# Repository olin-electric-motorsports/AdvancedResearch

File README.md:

# AdvancedResearch

2020 Advanced Research

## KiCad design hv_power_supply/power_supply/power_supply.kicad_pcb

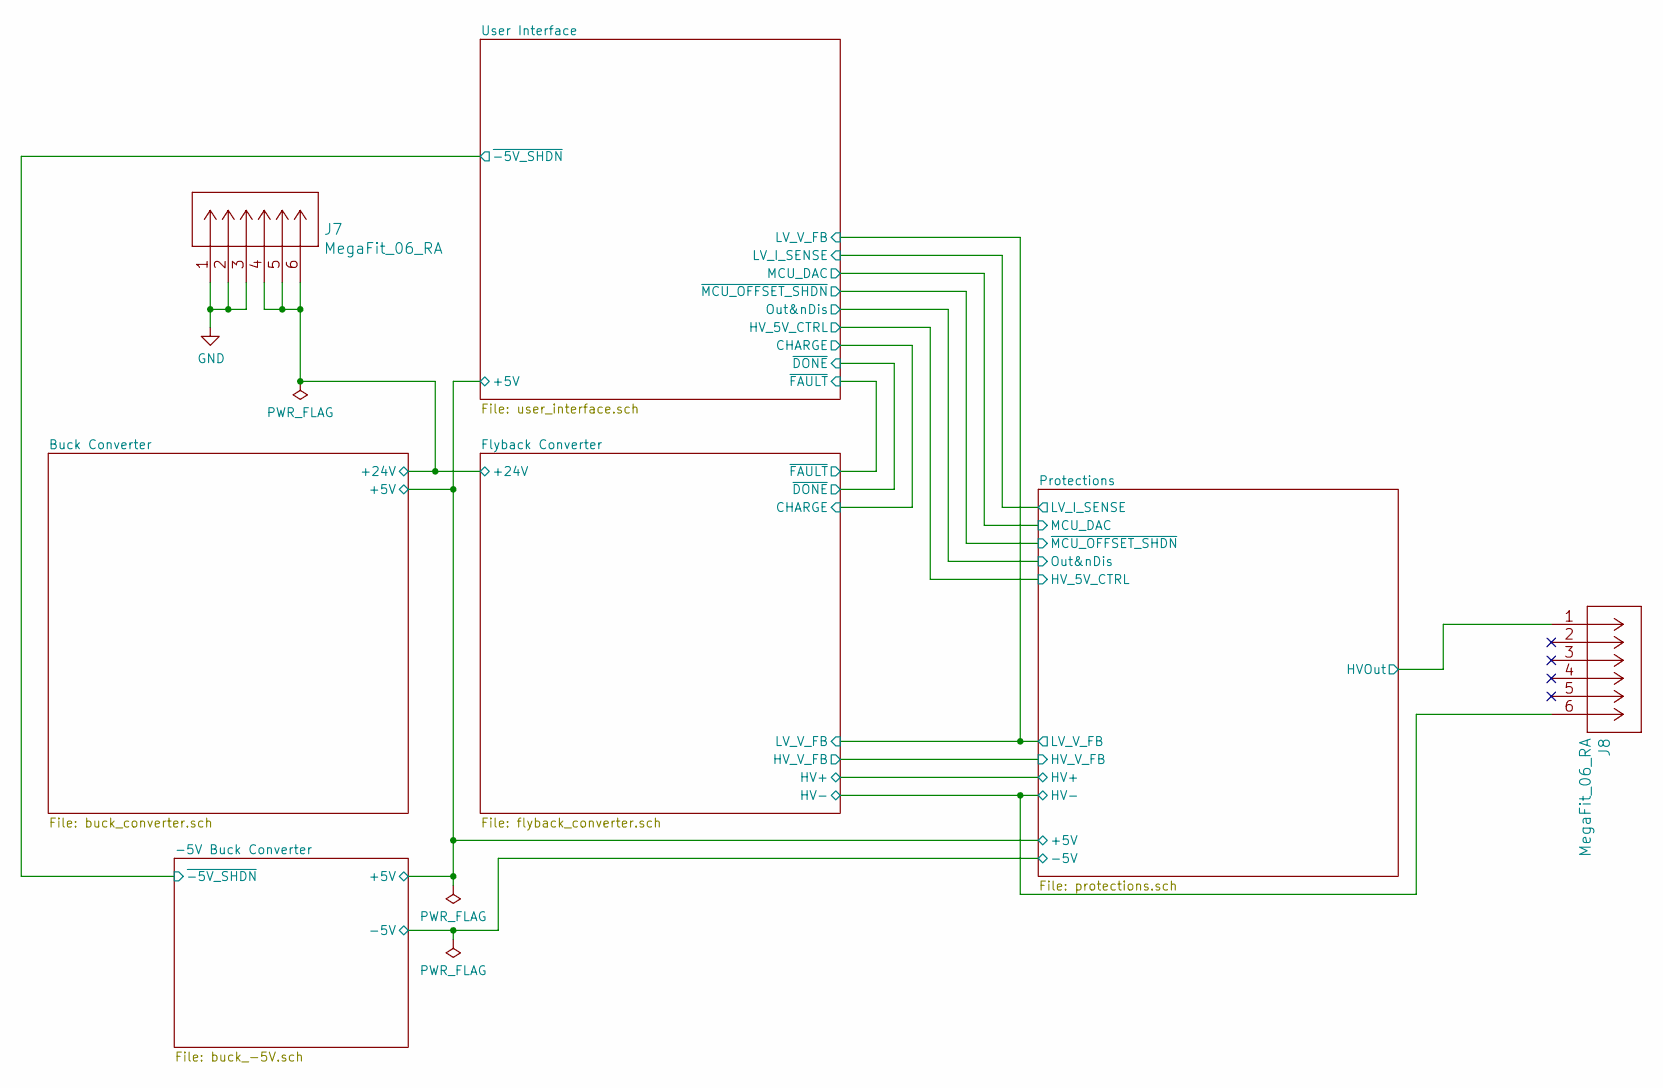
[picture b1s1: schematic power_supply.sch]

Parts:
J7, J8: MegaFit_06_RA; MPN 0768250006

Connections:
/Buck Converter/+24V: J7.4, J7.5, J7.6; also elsewhere on the board
/Flyback Converter/HV-: J8.6; also elsewhere on the board
/Protections/HVOut: J8.1; also elsewhere on the board
GND: J7.1, J7.2, J7.3; also elsewhere on the board

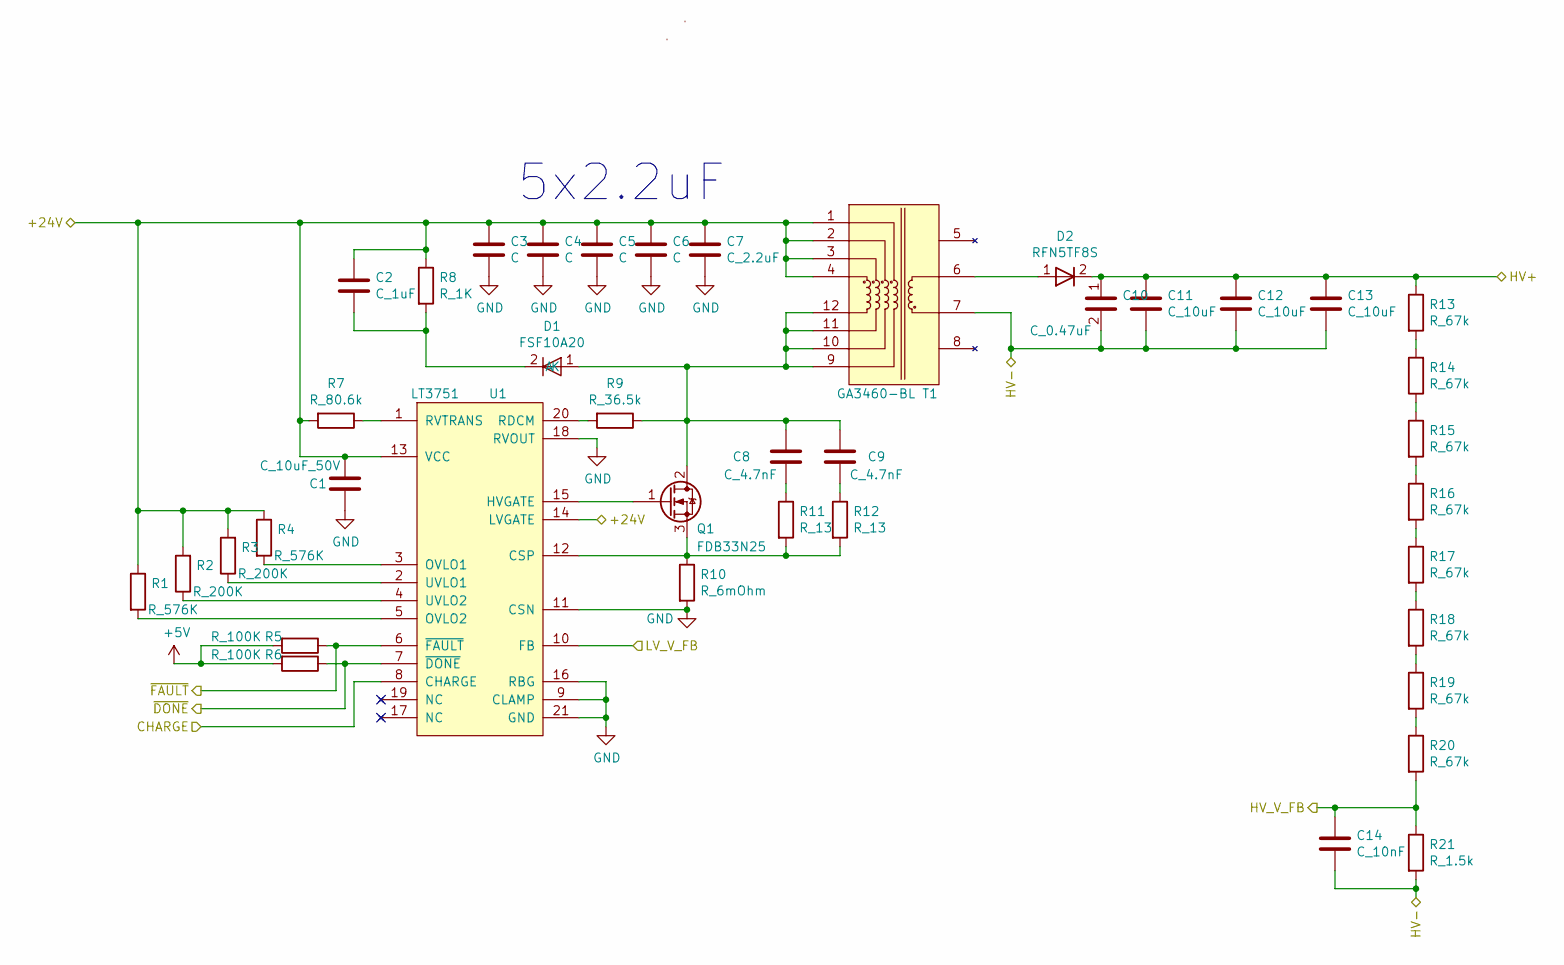
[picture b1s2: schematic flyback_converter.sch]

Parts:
C1: C_10uF_50V; C_0805_OEM; MPN GRM21BR61H106KE43L
C2: C_1uF; C_0805_OEM
C3, C4, C5, C6: C; C_0805_OEM
C7: C_2.2uF; C_0805_OEM
C8, C9: C_4.7nF; C_1206_OEM; MPN C1206C472KCRACTU
C10: C_0.47uF; 1812(4532Metric); MPN C4532X7T2W474K230KA
C11, C12, C13: C_10uF; C_10uF_450V
C14: C_10nF; C_0805_OEM; MPN 1276-1015-1-ND
D1: FSF10A20; TO-220NFM; MPN FSF10A20
D2: RFN5TF8S; TO-220NFM
Q1: FDB33N25; D2PAK; MPN FDB33N25TM
R1, R4: R_576K; R_0805_OEM; MPN 541-576KCCT-ND
R2, R3: R_200K; R_0805_OEM; MPN P300KDACT-ND
R5, R6: R_100K; R_0805_OEM; MPN P100KCCT-ND
R7: R_80.6k; R_0805_OEM; MPN RT0805BRD0780K6L
R8: R_1K; R_2512_OEM; MPN CHP2512-FX-1001ELF
R9: R_36.5k; R_0805_OEM; MPN RT0805BRD0736K5L
R10: R_6mOhm; R_2512_LARGE; MPN LRMAP2512-R006FT4
R11, R12: R_13; R_2512_LARGE; MPN 352113RFT
R13, R14, R15, R16, R17, R18, R19, R20: R_67k; R_0805_OEM; MPN CRCW080567K0FKTA
R21: R_1.5k; R_2010_Vishay; MPN CRCW20101K50FKEF
T1: GA3460-BL; MPN 994-GA3460-BL
U1: LT3751; TSSOP-20_EXPOSED_PAD; MPN LT3751EFE#TRPBF

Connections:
+5V: R5.2, R6.2; also elsewhere on the board
/Buck Converter/+24V: C1.2, C2.1, C3.1, C4.1, C5.1, C6.1, C7.1, R1.1, R2.2, R3.2, R4.1, R7.2, R8.1, T1.1, T1.2, T1.3, T1.4, U1.13 (VCC), U1.14 (LVGATE); also elsewhere on the board
/Flyback Converter/CHARGE: U1.8 (CHARGE); also elsewhere on the board
/Flyback Converter/HV+: C10.1, C11.1, C12.1, C13.1, D2.2, R13.1; also elsewhere on the board
/Flyback Converter/HV-: C10.2, C11.2, C12.2, C13.2, C14.2, R21.2, T1.7; also elsewhere on the board
/Flyback Converter/HV_V_FB: C14.1, R20.2, R21.1; also elsewhere on the board
/Flyback Converter/LV_V_FB: U1.10 (FB); also elsewhere on the board
/Flyback Converter/~DONE: R6.1, U1.7 (~DONE); also elsewhere on the board
/Flyback Converter/~FAULT: R5.1, U1.6 (~FAULT); also elsewhere on the board
GND: C1.1, C3.2, C4.2, C5.2, C6.2, C7.2, R10.2, U1.9 (CLAMP), U1.11 (CSN), U1.16 (RBG), U1.18 (RVOUT), U1.21 (GND); also elsewhere on the board
unnamed: C2.2, D1.2 (K), R8.2
unnamed: C8.1, C9.1, D1.1 (A), Q1.2, R9.1, T1.9, T1.10, T1.11, T1.12
unnamed: C8.2, R11.1
unnamed: C9.2, R12.1
unnamed: D2.1, T1.6
unnamed: Q1.1, U1.15 (HVGATE)
unnamed: Q1.3, R10.1, R11.2, R12.2, U1.12 (CSP)
unnamed: R1.2, U1.5 (OVLO2)
unnamed: R2.1, U1.4 (UVLO2)
unnamed: R3.1, U1.2 (UVLO1)
unnamed: R4.2, U1.3 (OVLO1)
unnamed: R7.1, U1.1 (RVTRANS)
unnamed: R9.2, U1.20 (RDCM)
unnamed: R13.2, R14.2
unnamed: R14.1, R15.1
unnamed: R15.2, R16.1
unnamed: R16.2, R17.1
unnamed: R17.2, R18.1
unnamed: R18.2, R19.1
unnamed: R19.2, R20.1

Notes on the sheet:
5x2.2uF

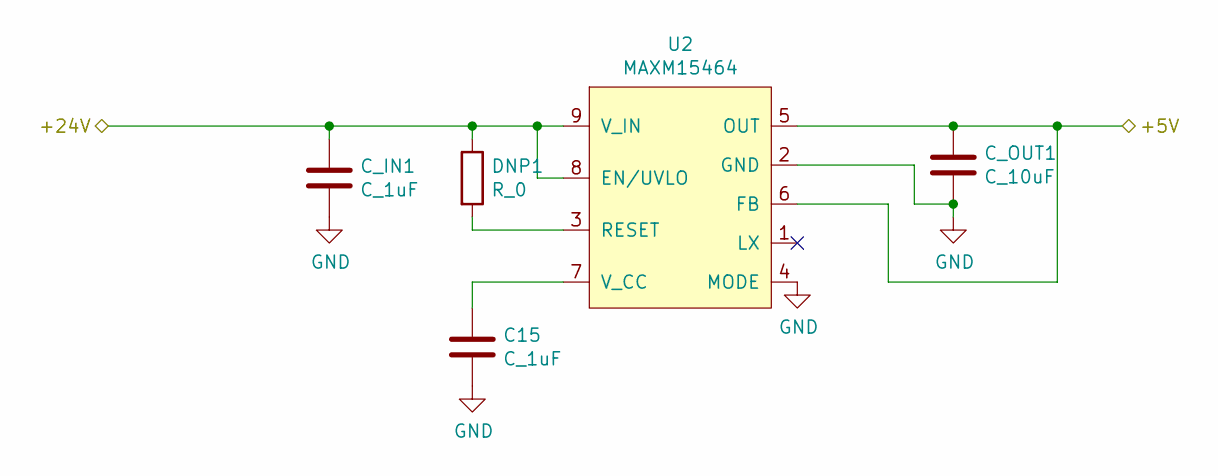
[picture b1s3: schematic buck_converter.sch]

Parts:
C15: C_1uF; C_0805_OEM
C_IN1: C_1uF; C_0805_OEM
C_OUT1: C_10uF; C_0805_OEM; MPN 1276-1052-1-ND
DNP1: R_0; R_0603_1608Metric; MPN P0.0GCT-ND
U2: MAXM15464; MPN MAXM15464AMB+

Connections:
+5V: C_OUT1.1, U2.5 (OUT), U2.6 (FB); also elsewhere on the board
/Buck Converter/+24V: C_IN1.1, DNP1.1, U2.8 (EN/UVLO), U2.9 (V_IN); also elsewhere on the board
GND: C15.2, C_IN1.2, C_OUT1.2, U2.2 (GND), U2.4 (MODE); also elsewhere on the board
unnamed: C15.1, U2.7 (V_CC)
unnamed: DNP1.2, U2.3 (RESET)

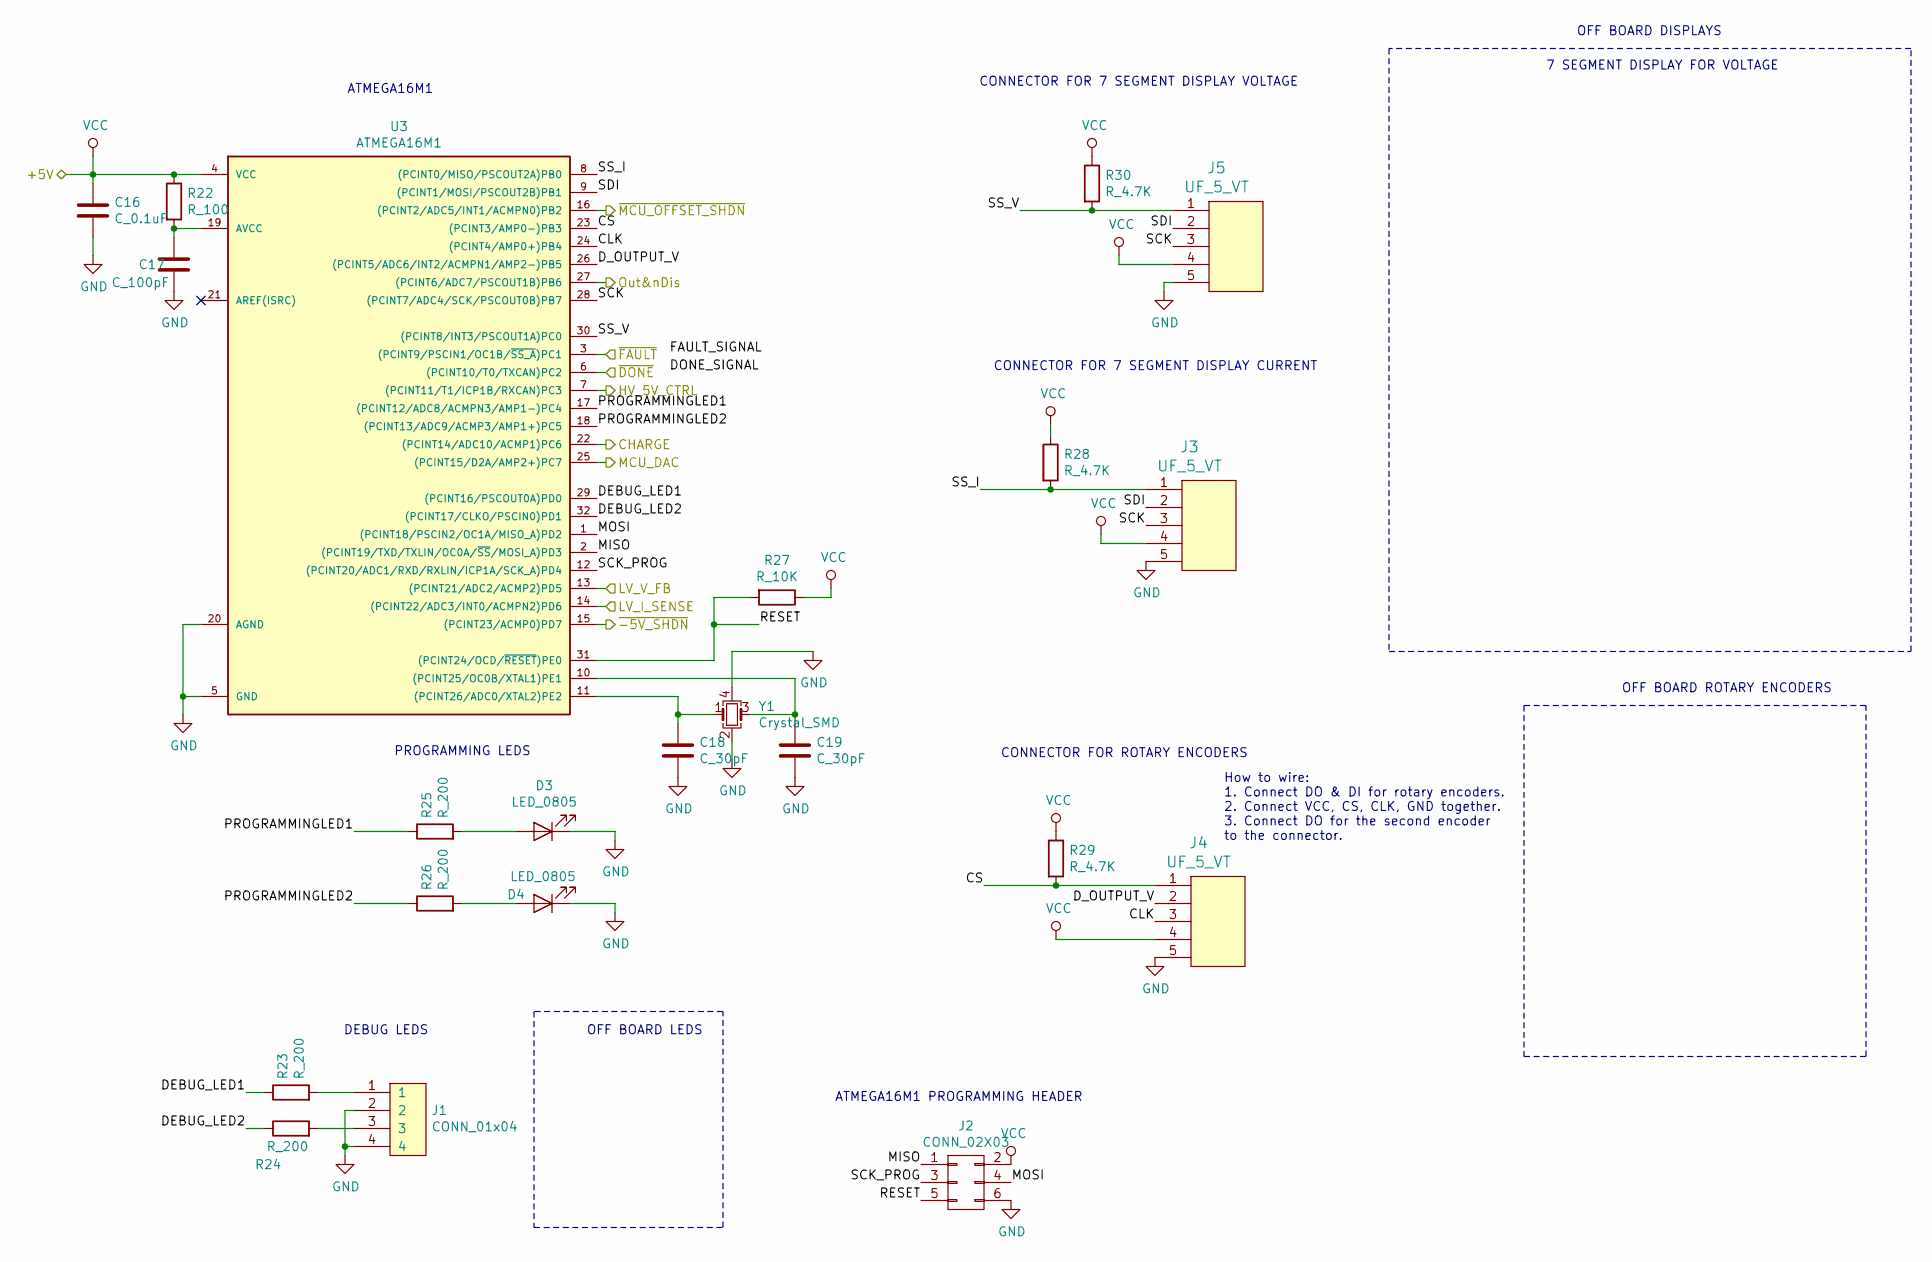
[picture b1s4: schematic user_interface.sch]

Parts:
C16: C_0.1uF; C_0805_OEM; MPN 478-3352-1-ND
C17: C_100pF; C_0805_OEM; MPN 732-7852-1-ND
C18, C19: C_30pF; C_0805_OEM; MPN 1276-1130-1-ND
D3, D4: LED_0805; LED_0805_OEM; MPN 475-1410-1-ND
J1: CONN_01x04; Pin_Header_Straight_1x04_Pitch2.54mm; MPN 732-5317-ND
J2: CONN_02X03; Pin_Header_Straight_2x03; MPN 609-3234-ND
J3, J4, J5: UF_5_VT; Ultrafit_5; MPN WM11667-ND
R22: R_100; R_0805_OEM; MPN RNCP0805FTD100RCT-ND
R23, R24, R25, R26: R_200; R_0805_OEM; MPN RMCF0805JT200RCT-ND
R27: R_10K; R_0805_OEM; MPN CRS0805-FX-1002ELFCT-ND
R28, R29, R30: R_4.7K; R_0805_OEM; MPN 311-4.7KARCT-ND
U3: ATMEGA16M1; TQFP-32_7x7mm_Pitch0.8mm; MPN ATMEGA16M1-AU-ND
Y1: Crystal_SMD; Crystal_SMD_FA238; MPN 887-1125-1-ND

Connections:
+5V: C16.1, J2.2, J3.4, J4.4, J5.4, R22.1, R27.1, R28.1, R29.1, R30.1, U3.4 (VCC); also elsewhere on the board
/-5V Buck Converter/~-5V_SHDN: U3.15 ((PCINT23/ACMP0)PD7); also elsewhere on the board
/Flyback Converter/CHARGE: U3.22 ((PCINT14/ADC10/ACMP1)PC6); also elsewhere on the board
/Flyback Converter/LV_V_FB: U3.13 ((PCINT21/ADC2/ACMP2)PD5); also elsewhere on the board
/Flyback Converter/~DONE: U3.6 ((PCINT10/T0/TXCAN)PC2); also elsewhere on the board
/Flyback Converter/~FAULT: U3.3 ((PCINT9/PSCIN1/OC1B/~SS_A~)PC1); also elsewhere on the board
/Protections/HV_5V_CTRL: U3.7 ((PCINT11/T1/ICP1B/RXCAN)PC3); also elsewhere on the board
/Protections/LV_I_SENSE: U3.14 ((PCINT22/ADC3/INT0/ACMPN2)PD6); also elsewhere on the board
/Protections/MCU_DAC: U3.25 ((PCINT15/D2A/AMP2+)PC7); also elsewhere on the board
/Protections/Out&nDis: U3.27 ((PCINT6/ADC7/PSCOUT1B)PB6); also elsewhere on the board
/Protections/~MCU_OFFSET_SHDN: U3.16 ((PCINT2/ADC5/INT1/ACMPN0)PB2); also elsewhere on the board
/User Interface/CLK: J4.3, U3.24 ((PCINT4/AMP0+)PB4)
/User Interface/CS: J4.1, R29.2, U3.23 ((PCINT3/AMP0-)PB3)
/User Interface/DEBUG_LED1: R23.1, U3.29 ((PCINT16/PSCOUT0A)PD0)
/User Interface/DEBUG_LED2: R24.1, U3.32 ((PCINT17/CLKO/PSCIN0)PD1)
/User Interface/D_OUTPUT_V: J4.2, U3.26 ((PCINT5/ADC6/INT2/ACMPN1/AMP2-)PB5)
/User Interface/MISO: J2.1, U3.2 ((PCINT19/TXD/TXLIN/OC0A/~SS~/MOSI_A)PD3)
/User Interface/MOSI: J2.4, U3.1 ((PCINT18/PSCIN2/OC1A/MISO_A)PD2)
/User Interface/PROGRAMMINGLED1: R25.1, U3.17 ((PCINT12/ADC8/ACMPN3/AMP1-)PC4)
/User Interface/PROGRAMMINGLED2: R26.1, U3.18 ((PCINT13/ADC9/ACMP3/AMP1+)PC5)
/User Interface/RESET: J2.5, R27.2, U3.31 ((PCINT24/OCD/~RESET~)PE0)
/User Interface/SCK: J3.3, J5.3, U3.28 ((PCINT7/ADC4/SCK/PSCOUT0B)PB7)
/User Interface/SCK_PROG: J2.3, U3.12 ((PCINT20/ADC1/RXD/RXLIN/ICP1A/SCK_A)PD4)
/User Interface/SDI: J3.2, J5.2, U3.9 ((PCINT1/MOSI/PSCOUT2B)PB1)
/User Interface/SS_I: J3.1, R28.2, U3.8 ((PCINT0/MISO/PSCOUT2A)PB0)
/User Interface/SS_V: J5.1, R30.2, U3.30 ((PCINT8/INT3/PSCOUT1A)PC0)
GND: C16.2, C17.2, C18.2, C19.2, D3.1 (K), D4.1 (K), J1.2, J1.4, J2.6, J3.5, J4.5, J5.5, U3.5 (GND), U3.20 (AGND), Y1.2, Y1.4; also elsewhere on the board
unnamed: C17.1, R22.2, U3.19 (AVCC)
unnamed: C18.1, U3.11 ((PCINT26/ADC0/XTAL2)PE2), Y1.1
unnamed: C19.1, U3.10 ((PCINT25/OC0B/XTAL1)PE1), Y1.3
unnamed: D3.2 (A), R25.2
unnamed: D4.2 (A), R26.2
unnamed: J1.1, R23.2
unnamed: J1.3, R24.2

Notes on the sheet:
ATMEGA16M1
PROGRAMMING LEDS
ATMEGA16M1 PROGRAMMING HEADER
CONNECTOR FOR 7 SEGMENT DISPLAY VOLTAGE
CONNECTOR FOR 7 SEGMENT DISPLAY CURRENT
DEBUG LEDS
CONNECTOR FOR ROTARY ENCODERS
How to wire: 1. Connect DO & DI for rotary encoders. 2. Connect VCC, CS, CLK, GND together. 3. Connect DO for the second encoder to the connector.
OFF BOARD LEDS
OFF BOARD DISPLAYS
OFF BOARD ROTARY ENCODERS
7 SEGMENT DISPLAY FOR VOLTAGE

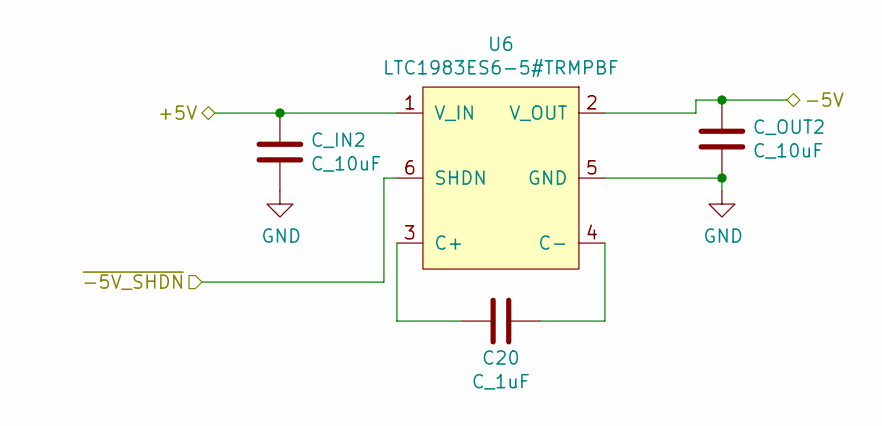
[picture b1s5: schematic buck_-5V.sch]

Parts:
C20: C_1uF; C_0805_OEM
C_IN2: C_10uF; C_0805_OEM; MPN 1276-1052-1-ND
C_OUT2: C_10uF; C_0805_OEM; MPN 1276-1052-1-ND
U6: LTC1983ES6-5#TRMPBF

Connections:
+5V: C_IN2.1, U6.1 (V_IN); also elsewhere on the board
/-5V Buck Converter/-5V: C_OUT2.1, U6.2 (V_OUT); also elsewhere on the board
/-5V Buck Converter/~-5V_SHDN: U6.6 (SHDN); also elsewhere on the board
GND: C_IN2.2, C_OUT2.2, U6.5 (GND); also elsewhere on the board
unnamed: C20.1, U6.3 (C+)
unnamed: C20.2, U6.4 (C-)

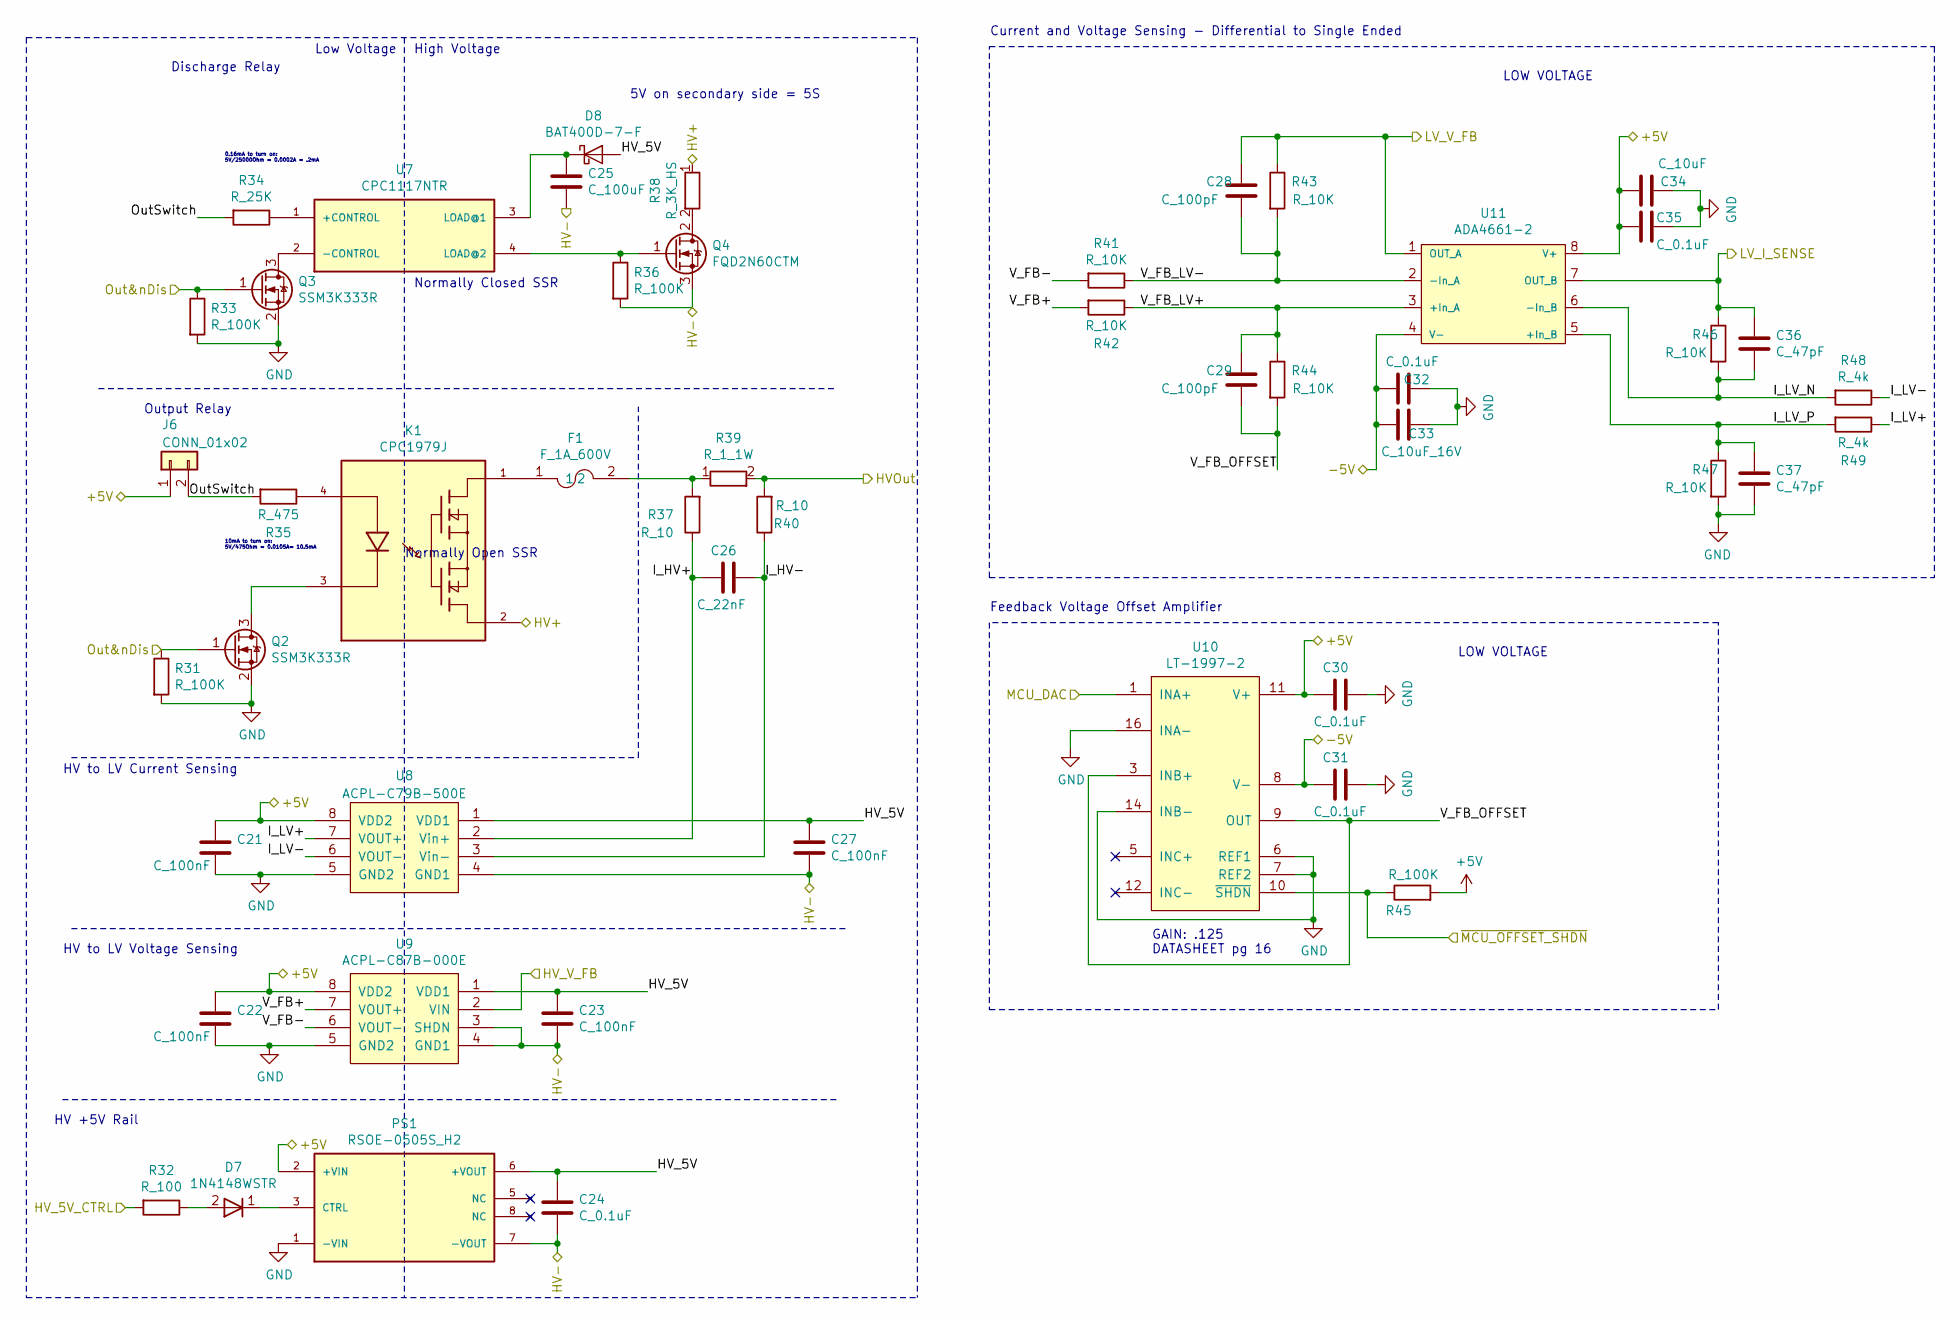
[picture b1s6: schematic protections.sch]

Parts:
C21, C22, C23, C27: C_100nF; C_0603_1608Metric; MPN 1276-6717-1-ND
C24, C30, C31, C32, C35: C_0.1uF; C_0805_OEM; MPN 478-3352-1-ND
C25: C_100uF; C_1812_4532Metric; MPN 445-1413-1-ND
C26: C_22nF; C_0805_OEM; MPN C0805C223G3GEC7800
C28, C29: C_100pF; C_0805_OEM; MPN 732-7852-1-ND
C33: C_10uF_16V; C_0805_OEM; MPN 1276-2399-1-ND
C34: C_10uF; C_0805_OEM; MPN 1276-2399-1-ND
C36, C37: C_47pF; C_0805_OEM; MPN CDR31BP470BKUS7185
D7: 1N4148WSTR; SOD-323; MPN 1N4148WSTR
D8: BAT400D-7-F; SOT-23-3_OEM
F1: F_1A_600V; Fuse_1A_600V
J6: CONN_01x02; PinHeader_1x02_P2.54mm_Vertical; MPN 732-5315-ND
K1: CPC1979J; TO381P2016X515X2916-4; PARTREV R10
PS1: RSOE-0505S_H2; H2; PARTREV 4/2020
Q2, Q3: SSM3K333R; SOT-23F; MPN SSM3K333RLFCT-ND
Q4: FQD2N60CTM; DPAK229P990X239-4N; MPN FDB33N25TM
R31, R33, R36, R45: R_100K; R_0805_OEM; MPN P100KCCT-ND
R32: R_100; R_0805_OEM; MPN RNCP0805FTD100RCT-ND
R34: R_25K; R_0805_OEM; MPN A124124CT-ND
R35: R_475; R_0805_OEM; MPN 311-475CRCT-ND
R37, R40: R_10; R_0805_OEM; MPN ERJ-P06F10R0V
R38: R_3K_HS; R_3k_HS_TO247; MPN AP1013KJ-ND
R39: R_1_1W; R_2512_LARGE
R41, R42, R43, R44, R46, R47: R_10K; R_0805_OEM; MPN CRS0805-FX-1002ELFCT-ND
R48, R49: R_4k; R_0805_OEM; MPN CRCW08054K00FKTA
U7: CPC1117NTR; SOIC254P610X218-4N
U8: ACPL-C79B-500E; SSO-8; MPN ACPL-C79B-500E
U9: ACPL-C87B-000E; SSO-8
U10: LT-1997-2; 16(12)-MSOP; MPN LT1997HMS-2#PBF
U11: ADA4661-2; SOP65P490X110-8N; MPN ADA4661-2ARMZ-RL

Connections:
+5V: C21.1, C22.1, C30.1, C34.1, C35.2, J6.1, PS1.2 (+VIN), R45.2, U8.8 (VDD2), U9.8 (VDD2), U10.11 (V+), U11.8 (V+); also elsewhere on the board
/-5V Buck Converter/-5V: C31.1, C32.1, C33.1, U10.8 (V-), U11.4 (V-); also elsewhere on the board
/Flyback Converter/HV+: K1.2, R38.1; also elsewhere on the board
/Flyback Converter/HV-: C23.2, C24.2, C25.2, C27.2, PS1.7 (-VOUT), Q4.3, R36.2, U8.4 (GND1), U9.3 (SHDN), U9.4 (GND1); also elsewhere on the board
/Flyback Converter/HV_V_FB: U9.2 (VIN); also elsewhere on the board
/Flyback Converter/LV_V_FB: C28.1, R43.1, U11.1 (OUT_A); also elsewhere on the board
/Protections/HVOut: R39.2, R40.2; also elsewhere on the board
/Protections/HV_5V: C23.1, C24.1, C27.1, D8.2 (A), PS1.6 (+VOUT), U8.1 (VDD1), U9.1 (VDD1)
/Protections/HV_5V_CTRL: R32.2; also elsewhere on the board
/Protections/I_HV+: C26.1, R37.1, U8.2 (Vin+)
/Protections/I_HV-: C26.2, R40.1, U8.3 (Vin-)
/Protections/I_LV+: R49.1, U8.7 (VOUT+)
/Protections/I_LV-: R48.1, U8.6 (VOUT-)
/Protections/I_LV_N: C36.2, R46.2, R48.2, U11.6 (-In_B)
/Protections/I_LV_P: C37.1, R47.1, R49.2, U11.5 (+In_B)
/Protections/LV_I_SENSE: C36.1, R46.1, U11.7 (OUT_B); also elsewhere on the board
/Protections/MCU_DAC: U10.1 (INA+); also elsewhere on the board
/Protections/Out&nDis: Q2.1 (G), Q3.1 (G), R31.1, R33.1; also elsewhere on the board
/Protections/OutSwitch: J6.2, R34.2, R35.2
/Protections/V_FB+: R42.2, U9.7 (VOUT+)
/Protections/V_FB-: R41.2, U9.6 (VOUT-)
/Protections/V_FB_LV+: C29.1, R42.1, R44.1, U11.3 (+In_A)
/Protections/V_FB_LV-: C28.2, R41.1, R43.2, U11.2 (-In_A)
/Protections/V_FB_OFFSET: C29.2, R44.2, U10.3 (INB+), U10.9 (OUT)
/Protections/~MCU_OFFSET_SHDN: R45.1, U10.10 (~SHDN); also elsewhere on the board
GND: C21.2, C22.2, C30.2, C31.2, C32.2, C33.2, C34.2, C35.1, C37.2, PS1.1 (-VIN), Q2.2 (S), Q3.2 (S), R31.2, R33.2, R47.2, U8.5 (GND2), U9.5 (GND2), U10.6 (REF1), U10.7 (REF2), U10.14 (INB-), U10.16 (INA-); also elsewhere on the board
unnamed: C25.1, D8.1 (K), U7.3 (LOAD@1)
unnamed: D7.1, PS1.3 (CTRL)
unnamed: D7.2, R32.1
unnamed: F1.1, K1.1
unnamed: F1.2, R37.2, R39.1
unnamed: K1.3, Q2.3 (D)
unnamed: K1.4, R35.1
unnamed: Q3.3 (D), U7.2 (-CONTROL)
unnamed: Q4.1, R36.1, U7.4 (LOAD@2)
unnamed: Q4.2, R38.2
unnamed: R34.1, U7.1 (+CONTROL)

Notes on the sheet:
Discharge Relay
Output Relay
5V on secondary side = 5S
Low Voltage
High Voltage
0.16mA to turn on: 5V/25000Ohm = 0.0002A = .2mA
Normally Closed SSR
Normally Open SSR
10mA to turn on: 5V/475Ohm = 0.0105A= 10.5mA
GAIN: .125 DATASHEET pg 16
HV to LV Current Sensing
HV to LV Voltage Sensing
HV +5V Rail
Feedback Voltage Offset Amplifier
LOW VOLTAGE
Current and Voltage Sensing - Differential to Single Ended

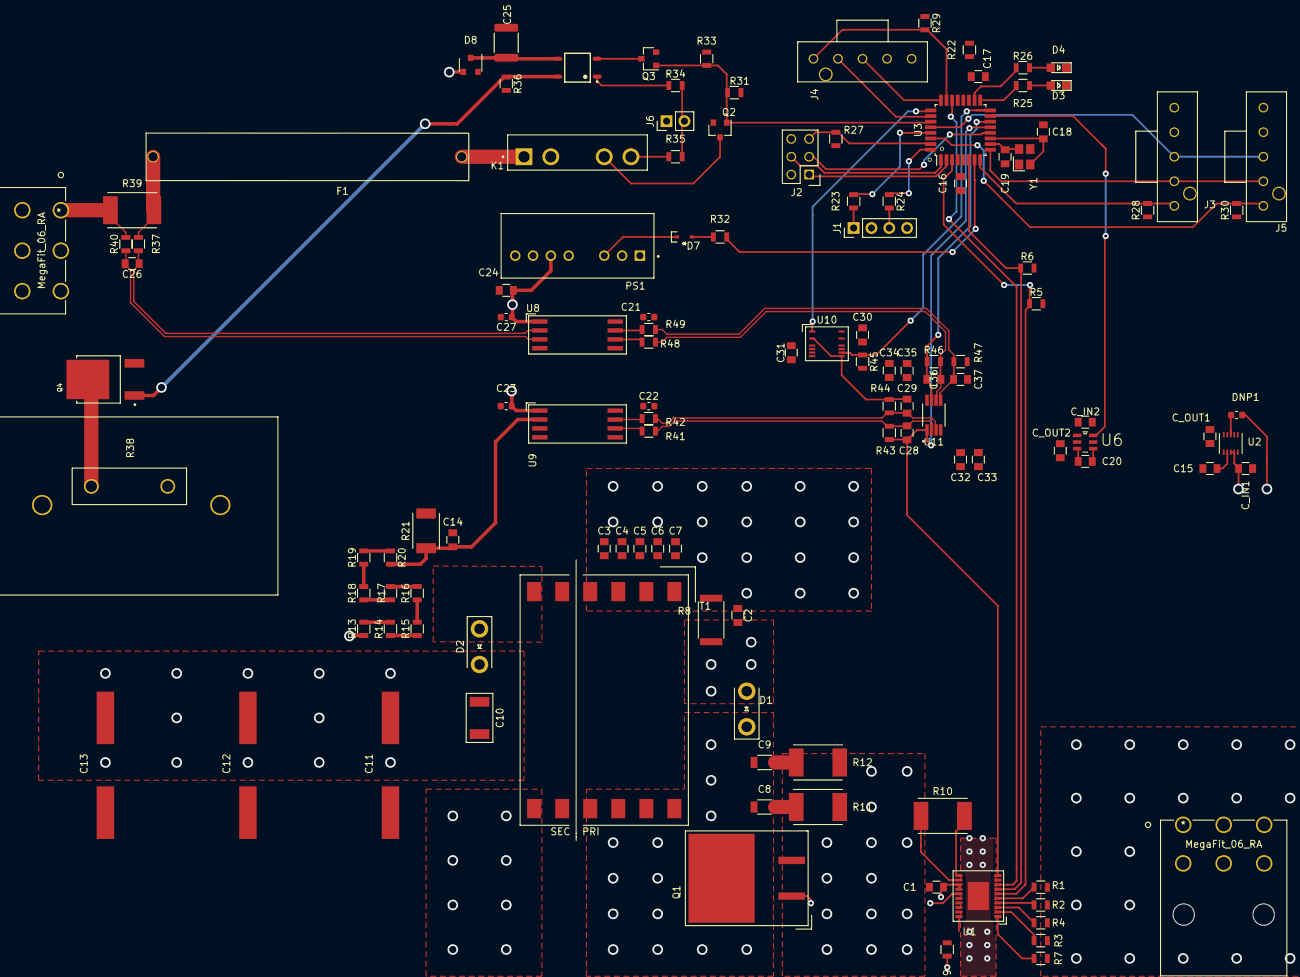
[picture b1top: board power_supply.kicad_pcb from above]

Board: 4 copper layers, 123 parts (0 on the bottom side), 88 nets.

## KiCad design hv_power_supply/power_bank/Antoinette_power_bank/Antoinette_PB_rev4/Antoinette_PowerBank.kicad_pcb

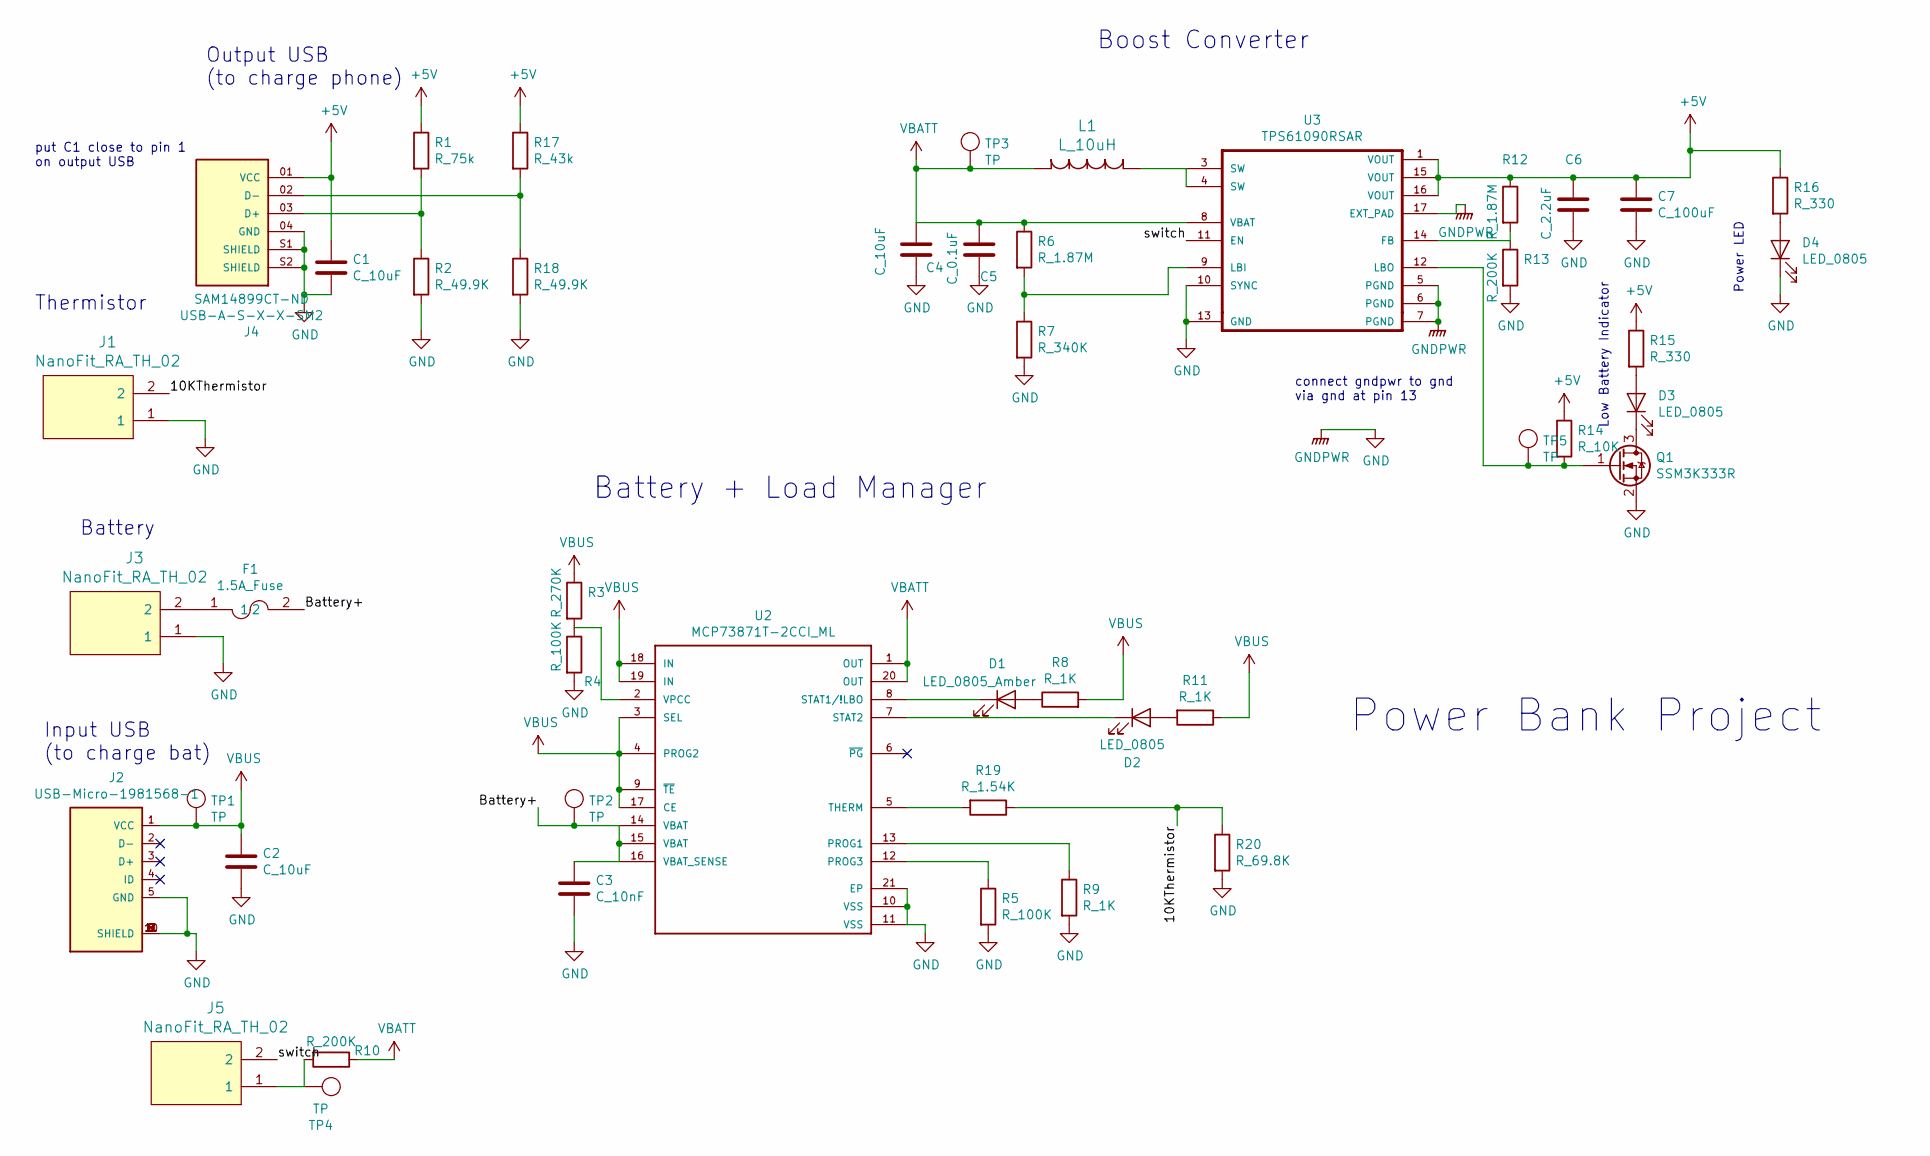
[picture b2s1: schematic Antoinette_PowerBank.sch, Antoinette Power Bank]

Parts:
C1, C2, C4: C_10uF; C_0805_OEM; MPN 1276-1052-1-ND
C3: C_10nF; C_0805_OEM; MPN 1276-1015-1-ND
C5: C_0.1uF; C_0805_OEM; MPN 478-3352-1-ND
C6: C_2.2uF; C_0805_OEM
C7: C_100uF; C_1812_4532Metric; MPN 445-1413-1-ND
D1: LED_0805_Amber; LED_0805_OEM; MPN L71517CT-ND
D2, D3, D4: LED_0805; LED_0805_OEM; MPN 475-1410-1-ND
F1: 1.5A_Fuse; Fuse_1206; MPN F1462CT-ND
J1, J3, J5: NanoFit_RA_TH_02; NanoFit_Molex_1x02x2.50mm_Angled_OEM; MPN WM14972-ND
J2: USB-Micro-1981568-1; TE_1981568-1; MPN 1981568-1
J4: USB-A-S-X-X-SM2; SAMTEC_USB-A-S-X-X-SM2; MPN SAM14899CT-ND
L1: L_10uH; BournsInductor; MPN SDE0805A-100M
Q1: SSM3K333R; SOT-23F; MPN SSM3K333RLFCT-ND
R1: R_75k; R_0805_OEM
R2, R18: R_49.9K; R_0805_OEM
R3: R_270K; R_0805_OEM; MPN P270KDACT-ND
R4, R5: R_100K; R_0805_OEM; MPN P100KCCT-ND
R6, R12: R_1.87M; R_0805_OEM; MPN RMCF0805FT1M82CT-ND
R7: R_340K; R_0805_OEM; MPN P300KDACT-ND
R8, R9, R11: R_1K; R_0805_OEM; MPN RNCP0805FTD1K00CT-ND
R10, R13: R_200K; R_0805_OEM; MPN P300KDACT-ND
R14: R_10K; R_0805_OEM; MPN CRS0805-FX-1002ELFCT-ND
R15, R16: R_330; R_0805_OEM; MPN RMCF0805FT330RCT-ND
R17: R_43k; R_0805_OEM
R19: R_1.54K; R_0805_OEM; MPN ERJ-6ENF1541V
R20: R_69.8K; R_0805_OEM; MPN ERJ-6ENF6982V
TP1, TP2, TP3, TP4, TP5: TP; tp_1.6mm; MPN 36-5006-ND
U2: MCP73871T-2CCI_ML; MCP73871T
U3: TPS61090RSAR

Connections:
+5V: C1.1, C6.1, C7.1, J4.01 (VCC), R1.1, R12.1, R14.1, R15.1, R16.1, R17.1, U3.1 (VOUT), U3.15 (VOUT), U3.16 (VOUT)
+BATT: C4.1, C5.1, L1.2, R6.1, R10.1, TP3.1, U2.1 (OUT), U2.20 (OUT), U3.8 (VBAT)
/10KThermistor: J1.2, R19.1, R20.1
/Battery+: C3.1, F1.2, TP2.1, U2.14 (VBAT), U2.15 (VBAT), U2.16 (VBAT_SENSE)
/switch: J5.2, U3.11 (EN)
GND: C1.2, C2.2, C3.2, C4.2, C5.2, C6.2, C7.2, D4.1 (K), J1.1, J2.5 (GND), J2.6 (SHIELD), J2.7 (SHIELD), J2.8 (SHIELD), J2.9 (SHIELD), J2.10 (SHIELD), J2.11 (SHIELD), J3.1, J4.04 (GND), J4.S1 (SHIELD), J4.S2 (SHIELD), Q1.2 (S), R2.2, R4.2, R5.2, R7.2, R9.2, R13.2, R18.2, R20.2, U2.10 (VSS), U2.11 (VSS), U2.21 (EP), U3.5 (PGND), U3.6 (PGND), U3.7 (PGND), U3.10 (SYNC), U3.13 (GND), U3.17 (EXT_PAD)
unnamed: D1.1 (K), U2.8 (STAT1/!LBO)
unnamed: D1.2 (A), R8.1
unnamed: D2.1 (K), U2.7 (STAT2)
unnamed: D2.2 (A), R11.2
unnamed: D3.1 (K), Q1.3 (D)
unnamed: D3.2 (A), R15.2
unnamed: D4.2 (A), R16.2
unnamed: F1.1, J3.2
unnamed: J4.02 (D-), R17.2, R18.1
unnamed: J4.03 (D+), R1.2, R2.1
unnamed: J5.1, R10.2, TP4.1
unnamed: L1.1, U3.3 (SW), U3.4 (SW)
unnamed: Q1.1 (G), R14.2, TP5.1, U3.12 (LBO)
unnamed: R3.2, R4.1, U2.2 (VPCC)
unnamed: R5.1, U2.12 (PROG3)
unnamed: R6.2, R7.1, U3.9 (LBI)
unnamed: R9.1, U2.13 (PROG1)
unnamed: R12.2, R13.1, U3.14 (FB)
unnamed: R19.2, U2.5 (THERM)
VBUS: C2.1, J2.1 (VCC), R3.1, R8.2, R11.1, TP1.1, U2.3 (SEL), U2.4 (PROG2), U2.9 (~TE~), U2.17 (CE), U2.18 (IN), U2.19 (IN)

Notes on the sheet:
Output USB (to charge phone)
Thermistor
Battery
Input USB (to charge bat)
connect gndpwr to gnd via gnd at pin 13
Boost Converter
Low Battery Indicator
Power LED
Battery + Load Manager
Power Bank Project
put C1 close to pin 1 on output USB

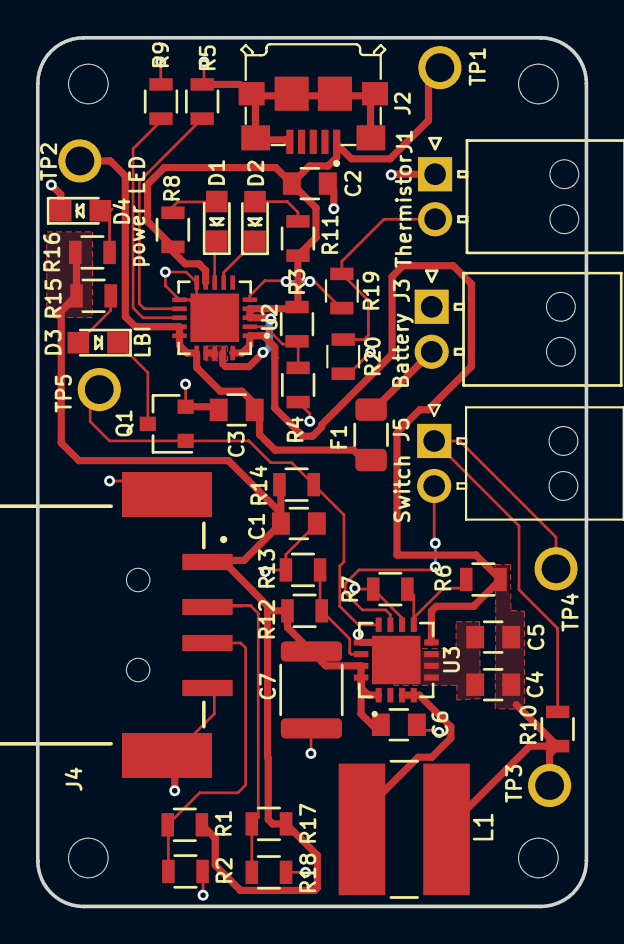
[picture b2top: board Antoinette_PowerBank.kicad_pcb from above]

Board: 2 copper layers, 30.5 x 48.3 mm, 47 parts (0 on the bottom side), 26 nets.

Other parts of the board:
R: MountingHole_2.2mm_M2

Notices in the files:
parts and their libraries:
Copyright 2016 Accelerated Designs. All rights reserved.
